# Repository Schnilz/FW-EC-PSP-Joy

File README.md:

# PSP Joystick Framework Laptop Expansion Card

A joystick expansion card with 2 buttons and the low profile psp joystick.

<p float="left" style="display: flex; flex-wrap: wrap; align-items: center;">
  &nbsp;
  
</p>

This uses the 10cent risc-v ch32v003 with  and its software-USB stack  to power this HID device. 

## PCB

<p float="left" style="display: flex; flex-wrap: wrap; align-items: center;">
  &nbsp;
  
</p>

## Thanks

Thanks to LeoDJ for open sourceing his  which this is based upon.

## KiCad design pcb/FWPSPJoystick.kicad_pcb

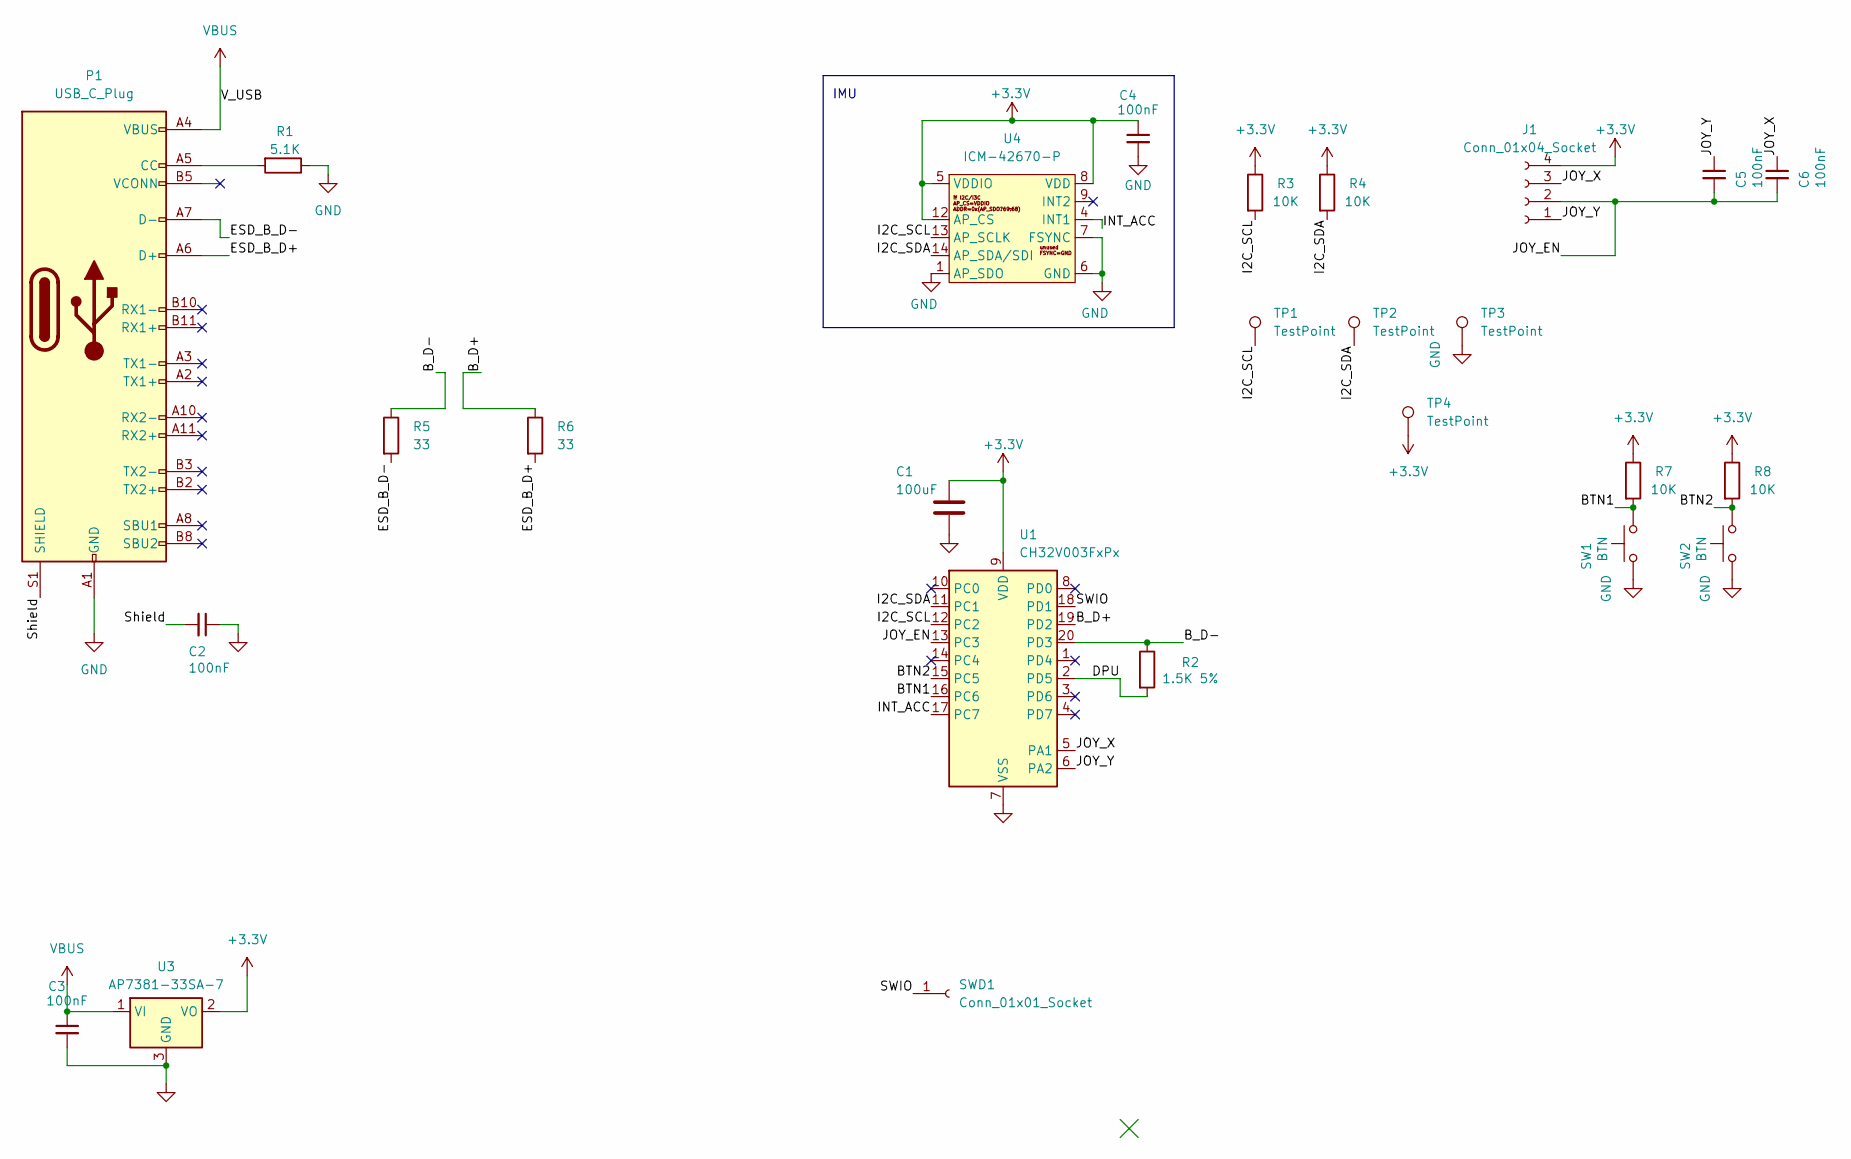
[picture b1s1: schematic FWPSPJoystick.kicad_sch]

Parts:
C1: 100uF; C_0805_2012Metric; LCSC C440198
C2, C5, C6: 100nF; C_0603_1608Metric; LCSC C14663
C3, C4: 100nF; C_0603_1608Metric
J1: Conn_01x04_Socket; pspjoystick_tht
P1: USB_C_Plug; USB_C_Plug_Molex_105444; LCSC C561769
R1: 5.1K; R_0603_1608Metric; LCSC C23186
R2: 1.5K 5%; R_0603_1608Metric; LCSC C23186
R3, R4, R7, R8: 10K; R_0603_1608Metric
R5, R6: 33; R_0603_1608Metric
SW1, SW2: BTN; TS21
SWD1: Conn_01x01_Socket; TestPoint_THTPad_D1.0mm_Drill0.5mm
TP1, TP2, TP3, TP4: TestPoint; TestPoint_Pad_D1.0mm
U1: CH32V003FxPx; TSSOP-20_4.4x6.5mm_P0.65mm
U3: AP7381-33SA-7; SOT-23
U4: ICM-42670-P; LGA-14_2.5x3x0.76mm

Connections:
+3.3V: C1.1, C4.1, J1.4, R3.1, R4.1, R7.1, R8.1, TP4.1, U1.9 (VDD), U3.2 (VO), U4.5 (VDDIO), U4.8 (VDD), U4.12 (AP_CS)
/BTN1: R7.2, SW1.2, U1.16 (PC6)
/BTN2: R8.2, SW2.2, U1.15 (PC5)
/B_D+: R6.1, U1.19 (PD2)
/B_D-: R2.1, R5.1, U1.20 (PD3)
/DPU: R2.2, U1.2 (PD5)
/ESD_B_D+: P1.A6 (D+), R6.2
/ESD_B_D-: P1.A7 (D-), R5.2
/I2C_SCL: R3.2, TP1.1, U1.12 (PC2), U4.13 (AP_SCLK)
/I2C_SDA: R4.2, TP2.1, U1.11 (PC1), U4.14 (AP_SDA/SDI)
/INT_ACC: U1.17 (PC7), U4.4 (INT1)
/JOY_EN: C5.2, C6.2, J1.2, U1.13 (PC3)
/JOY_X: C6.1, J1.3, U1.5 (PA1)
/JOY_Y: C5.1, J1.1, U1.6 (PA2)
/SWIO: SWD1.1, U1.18 (PD1)
/Shield: C2.2, P1.S1 (SHIELD)
GND: C1.2, C2.1, C3.2, C4.2, P1.A1 (GND), P1.A12 (GND), P1.B1 (GND), P1.B12 (GND), R1.1, SW1.1, SW2.1, TP3.1, U1.7 (VSS), U3.3 (GND), U4.1 (AP_SDO), U4.6 (GND), U4.7 (FSYNC)
unnamed: P1.A5 (CC), R1.2
VBUS: C3.1, P1.A4 (VBUS), P1.A9 (VBUS), P1.B4 (VBUS), P1.B9 (VBUS), U3.1 (VI)

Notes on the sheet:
IMU

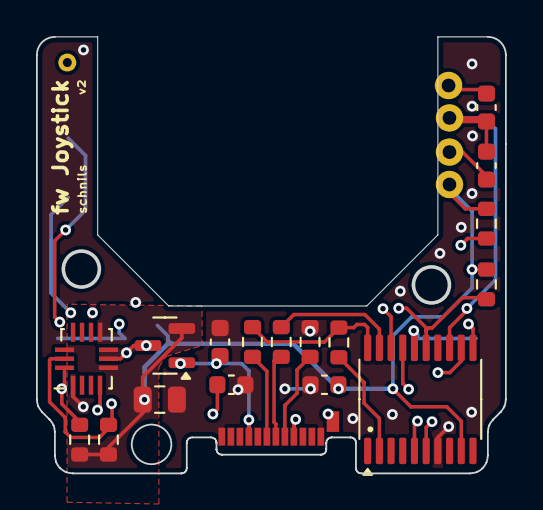
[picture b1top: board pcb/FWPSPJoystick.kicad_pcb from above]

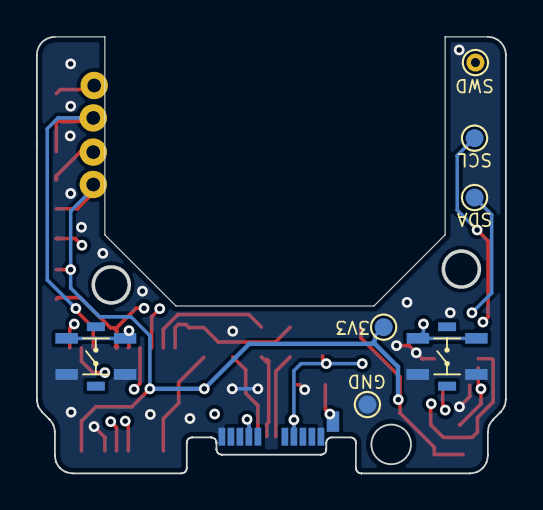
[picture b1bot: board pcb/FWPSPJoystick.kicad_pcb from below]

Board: 4 copper layers, 26.0 x 24.1 mm, 26 parts (7 on the bottom side), 19 nets.

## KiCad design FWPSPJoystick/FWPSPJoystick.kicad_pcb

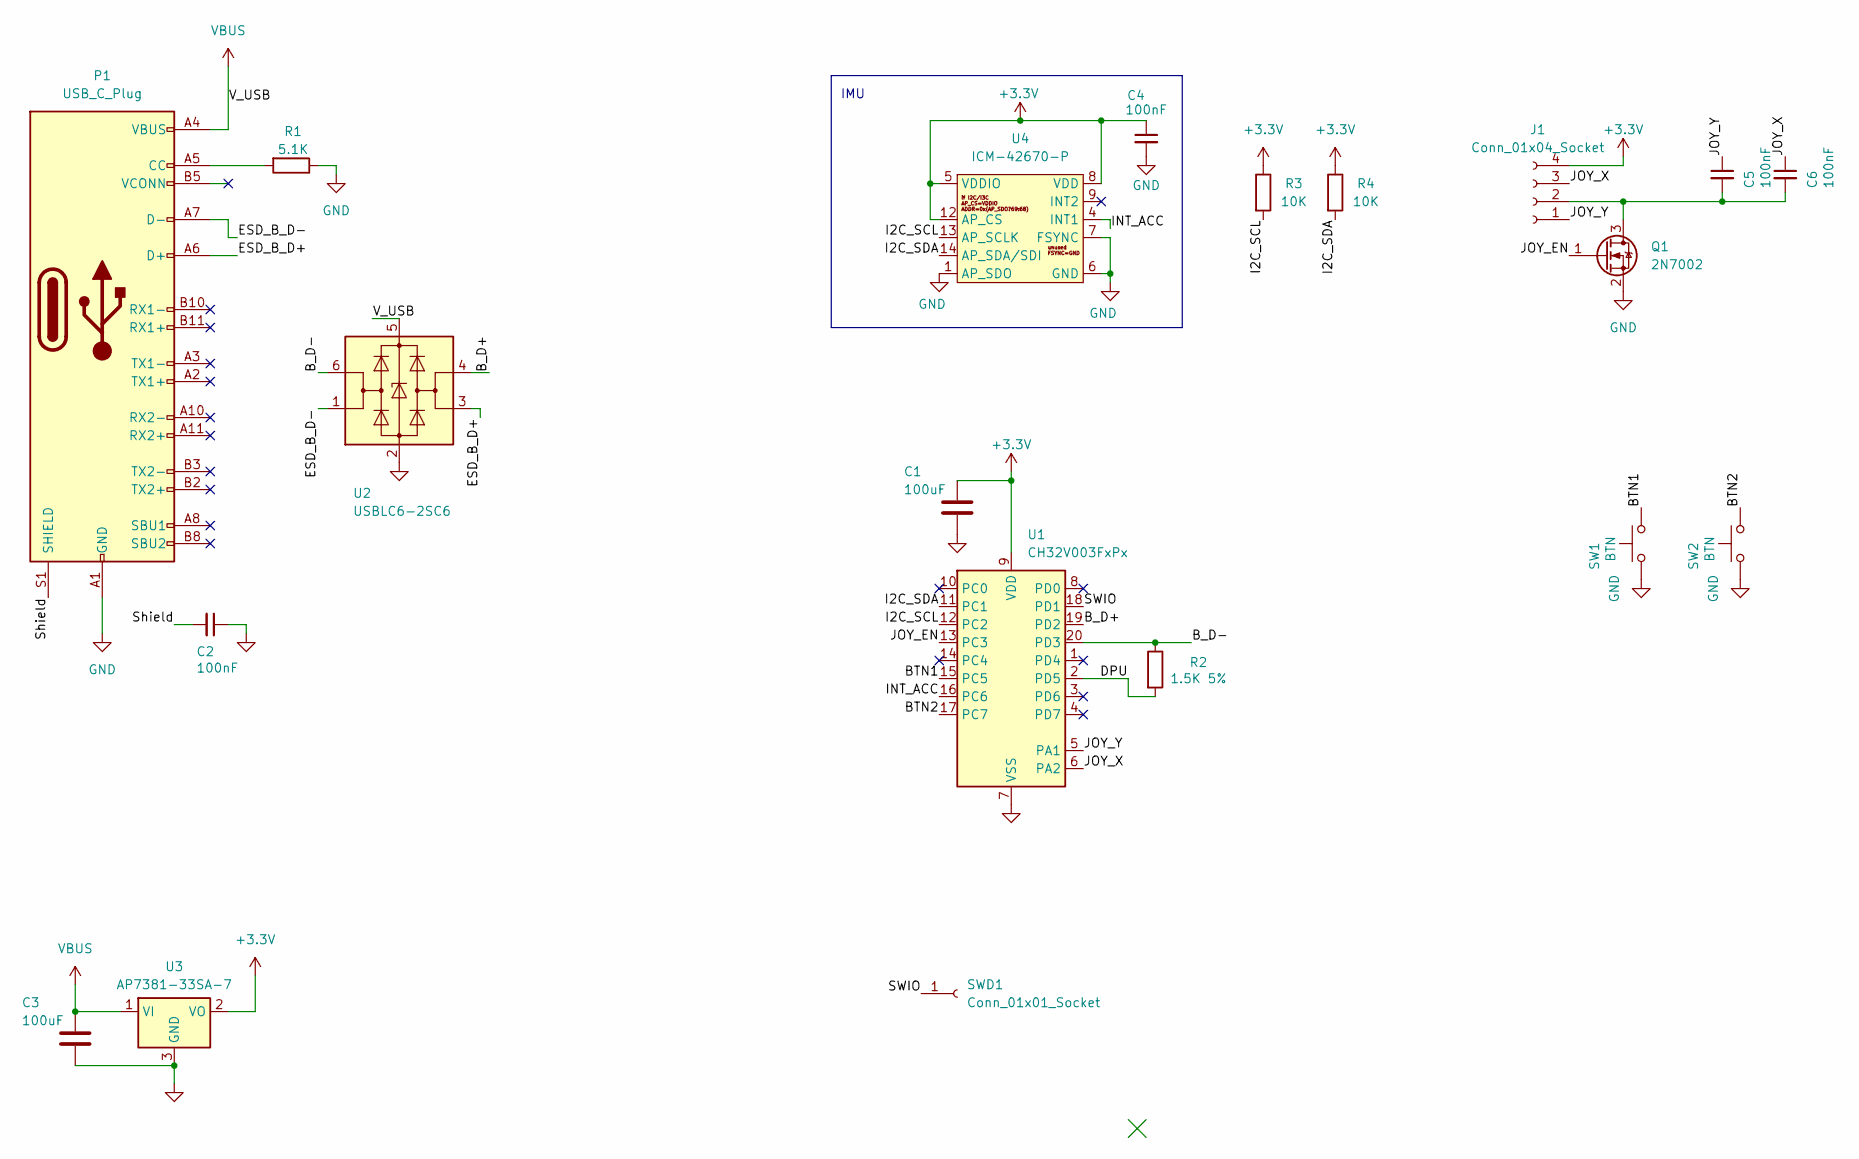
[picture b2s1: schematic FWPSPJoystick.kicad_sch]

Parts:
C1, C3: 100uF; C_0805_2012Metric; LCSC C440198
C2, C5, C6: 100nF; C_0603_1608Metric; LCSC C14663
C4: 100nF; C_0603_1608Metric
J1: Conn_01x04_Socket; pspjoystick_tht
P1: USB_C_Plug; USB_C_Plug_Molex_105444; LCSC C561769
Q1: 2N7002; SOT-23
R1: 5.1K; R_0603_1608Metric; LCSC C23186
R2: 1.5K 5%; R_0603_1608Metric; LCSC C23186
R3, R4: 10K; R_0603_1608Metric
SW1, SW2: BTN; TS21
SWD1: Conn_01x01_Socket; TestPoint_THTPad_D1.0mm_Drill0.5mm
U1: CH32V003FxPx; TSSOP-20_4.4x6.5mm_P0.65mm
U2: USBLC6-2SC6; SOT-23-6; LCSC C2687116
U3: AP7381-33SA-7; SOT-23
U4: ICM-42670-P; LGA-14_2.5x3x0.76mm

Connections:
+3.3V: C1.1, C4.1, J1.4, R3.1, R4.1, U1.9 (VDD), U3.2 (VO), U4.5 (VDDIO), U4.8 (VDD), U4.12 (AP_CS)
/BTN1: SW1.2, U1.15 (PC5)
/BTN2: SW2.2, U1.17 (PC7)
/B_D+: U1.19 (PD2), U2.4 (I/O2)
/B_D-: R2.1, U1.20 (PD3), U2.6 (I/O1)
/DPU: R2.2, U1.2 (PD5)
/ESD_B_D+: P1.A6 (D+), U2.3 (I/O2)
/ESD_B_D-: P1.A7 (D-), U2.1 (I/O1)
/I2C_SCL: R3.2, U1.12 (PC2), U4.13 (AP_SCLK)
/I2C_SDA: R4.2, U1.11 (PC1), U4.14 (AP_SDA/SDI)
/INT_ACC: U1.16 (PC6), U4.4 (INT1)
/JOY_EN: Q1.1 (G), U1.13 (PC3)
/JOY_X: C6.1, J1.3, U1.6 (PA2)
/JOY_Y: C5.1, J1.1, U1.5 (PA1)
/SWIO: SWD1.1, U1.18 (PD1)
/Shield: C2.2, P1.S1 (SHIELD)
GND: C1.2, C2.1, C3.2, C4.2, P1.A1 (GND), P1.A12 (GND), P1.B1 (GND), P1.B12 (GND), Q1.2 (S), R1.1, SW1.1, SW2.1, U1.7 (VSS), U2.2 (GND), U3.3 (GND), U4.1 (AP_SDO), U4.6 (GND), U4.7 (FSYNC)
unnamed: C5.2, C6.2, J1.2, Q1.3 (D)
unnamed: P1.A5 (CC), R1.2
VBUS: C3.1, P1.A4 (VBUS), P1.A9 (VBUS), P1.B4 (VBUS), P1.B9 (VBUS), U2.5 (VBUS), U3.1 (VI)

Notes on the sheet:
IMU

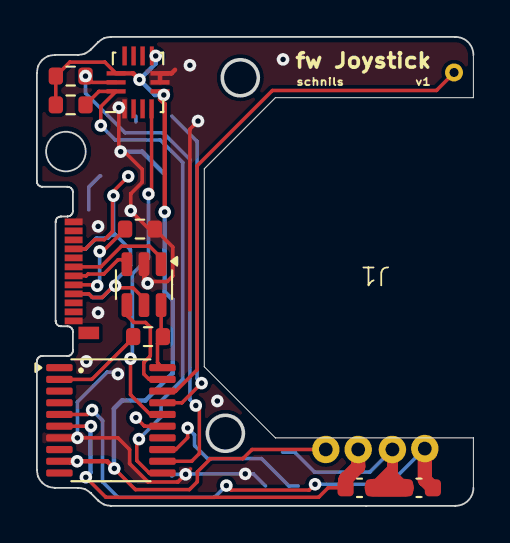
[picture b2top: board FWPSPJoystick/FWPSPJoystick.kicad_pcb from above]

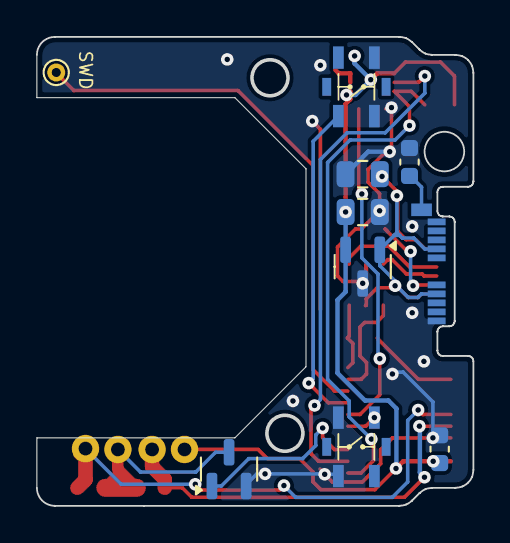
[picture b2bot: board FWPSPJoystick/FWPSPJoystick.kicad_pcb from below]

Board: 2 copper layers, 24.2 x 26.0 mm, 20 parts (9 on the bottom side), 20 nets.

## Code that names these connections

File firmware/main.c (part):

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static volatile uint8_t tsajoystick[3] = {0x00, 0x00, 0x00};

// #define STATUS_LED
// #define STATUS_LED_PIN PC3

void enter_sleep() {
  // enable power interface module clock
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      uptime_10ms = 0;
      last_usb_packet_10ms = STANDBY_AFTER_DURATION_10MS;
#if defined(PC3_STATUS_LED)
      funDigitalWrite(PC3, 0);
#endif
    }
  };
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  funPinMode(STATUS_LED_PIN, GPIO_CFGLR_OUT_2Mhz_OD);
  funDigitalWrite(STATUS_LED_PIN, 1);
#endif
  funPinMode(PC3, GPIO_CFGLR_OUT_2Mhz_OD);
  funDigitalWrite(PC3, 1);
#endif
  funPinMode(PC5, GPIO_CFGLR_IN_PUPD);
  funPinMode(PC7, GPIO_CFGLR_IN_PUPD);
  funDigitalWrite(PC5, 1);
  funDigitalWrite(PC7, 1);

  // PA1 is analog input chl 1
  funPinMode(PA1, GPIO_CFGLR_IN_ANALOG);
  // PA2 is analog input chl 0
  funPinMode(PA2, GPIO_CFGLR_IN_ANALOG);

  // Reset the ADC to init all regs
  RCC->APB2PRSTR |= RCC_APB2Periph_ADC1;
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  if (endp) {

#if defined(PC3_STATUS_LED)
    funDigitalWrite(PC3, 0);
#endif
    if (calibration_mode) {
      tsajoystick[2] = 0;
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    usb_send_data((const void *)tsajoystick, sizeof(tsajoystick), 0, sendtok);

#if defined(PC3_STATUS_LED)
    funDigitalWrite(PC3, 1);
#endif
    last_usb_packet_10ms = uptime_10ms;
  } else {
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
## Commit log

2024-12-30 initial Joystick version
2025-01-08 firmware
2025-08-22 save calibration to flash
